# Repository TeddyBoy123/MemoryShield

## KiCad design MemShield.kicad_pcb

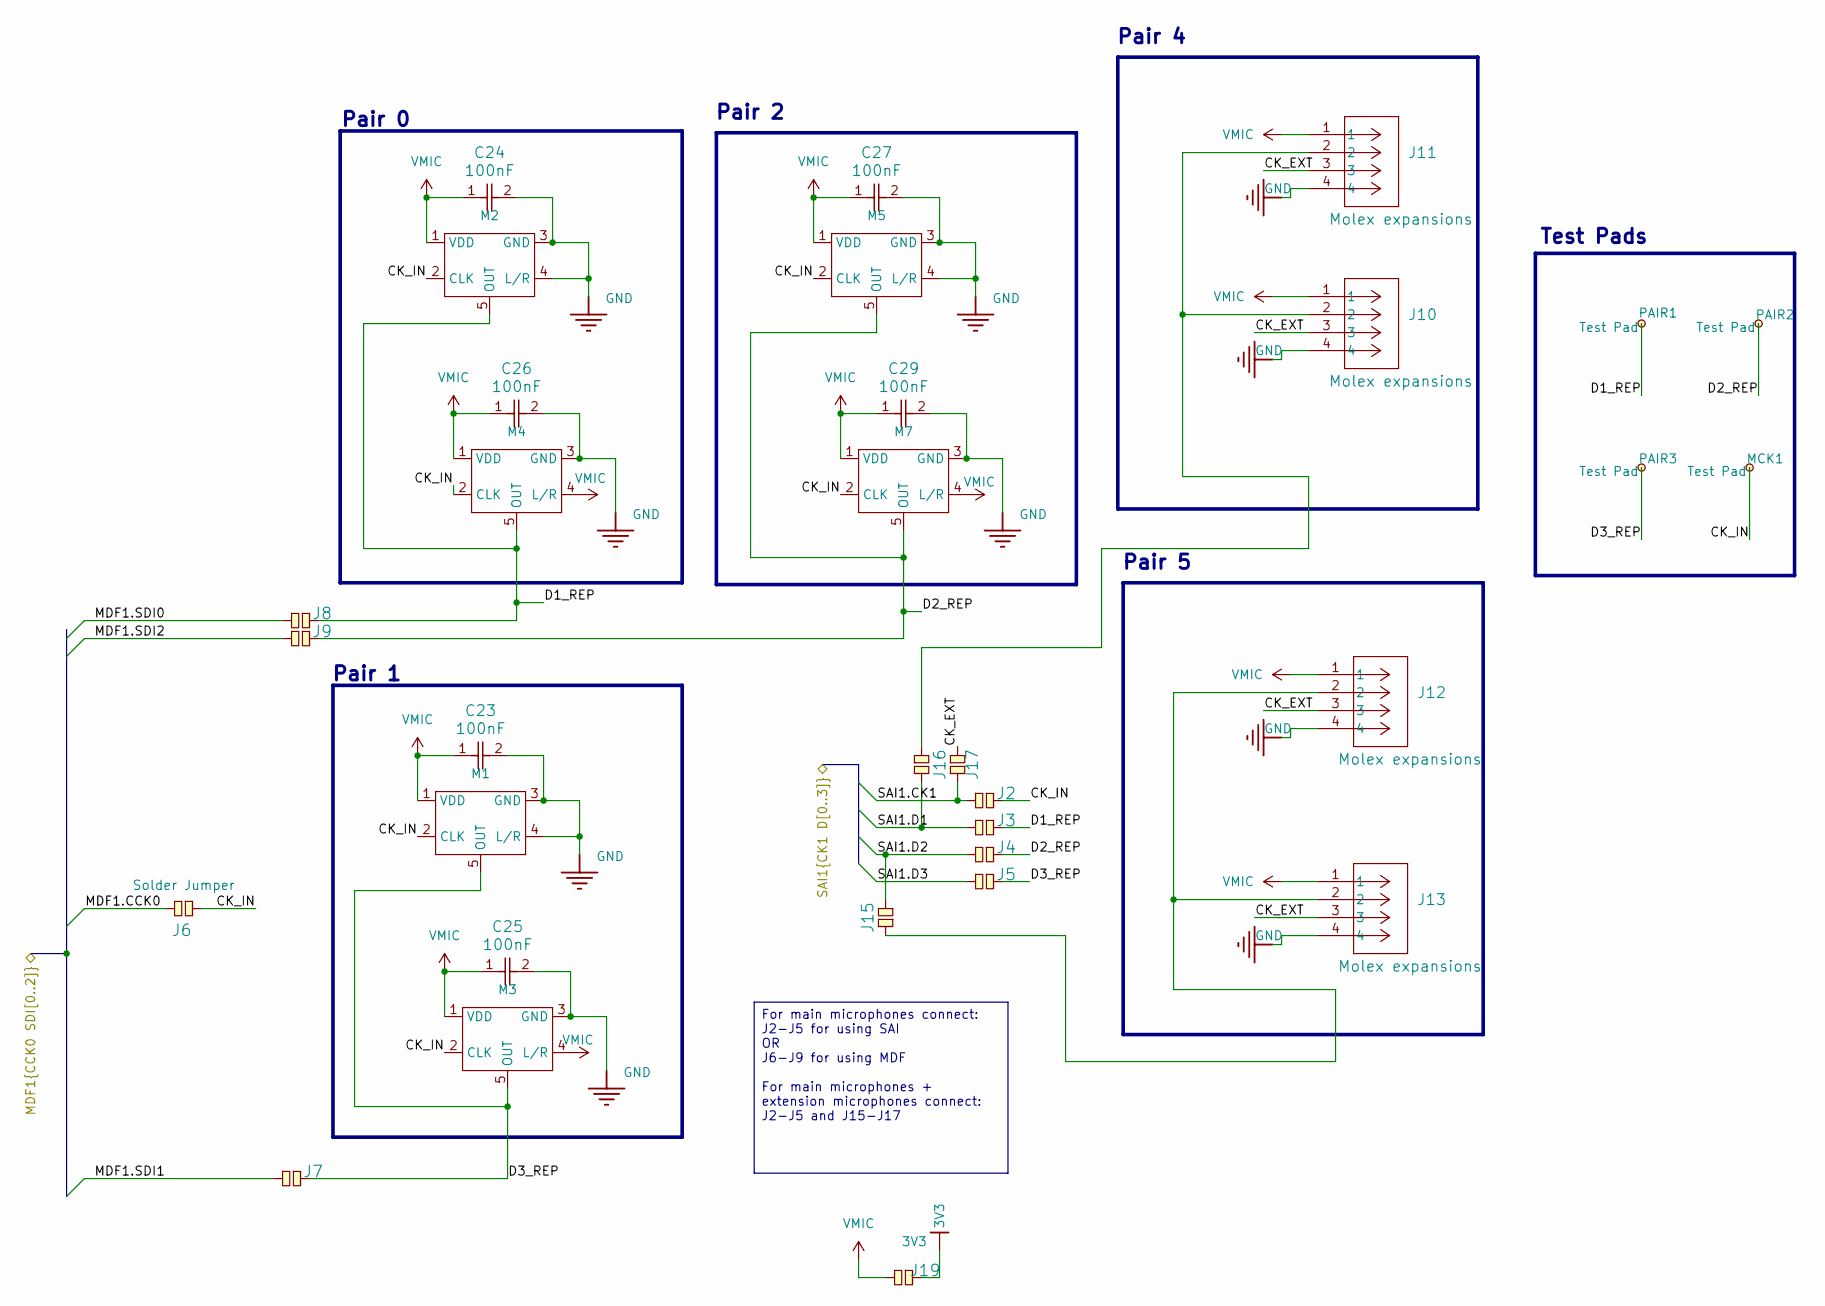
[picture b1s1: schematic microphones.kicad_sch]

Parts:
C23, C24, C25, C26, C27, C29: 100nF; CAP_0402_N_WAL
J2, J3, J4, J5, J6, J7, J8, J9, J15, J16, J17, J19: Solder Jumper; SolderJumper-2_P1.3mm_Open_RoundedPad1.0x1.5mm
J10, J11, J12, J13: Molex expansions; CONN04_530480410_MOL
M1, M2, M3, M4, M5, M7: Microphone; DMM-2627-B
MCK1: Test Pad; TestPoint_Pad_D1.0mm
PAIR1, PAIR2, PAIR3: Test Pad; TestPoint_Pad_D1.0mm

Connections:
3V3: J19.1; also elsewhere on the board
/Core/MDF1.CCK0: J6.2; also elsewhere on the board
/Core/MDF1.SDI0: J8.2; also elsewhere on the board
/Core/MDF1.SDI1: J7.2; also elsewhere on the board
/Core/MDF1.SDI2: J9.2; also elsewhere on the board
/Core/SAI1.CK1: J2.2, J17.2; also elsewhere on the board
/Core/SAI1.D1: J3.2, J16.2; also elsewhere on the board
/Core/SAI1.D2: J4.2, J15.2; also elsewhere on the board
/Core/SAI1.D3: J5.2; also elsewhere on the board
/microphones/CK_EXT: J10.3, J11.3, J12.3, J13.3, J17.1
/microphones/CK_IN: J2.1, J6.1, M1.2 (CLK), M2.2 (CLK), M3.2 (CLK), M4.2 (CLK), M5.2 (CLK), M7.2 (CLK), MCK1.1
/microphones/D1_REP: J3.1, J8.1, M2.5 (OUT), M4.5 (OUT), PAIR1.1
/microphones/D2_REP: J4.1, J9.1, M5.5 (OUT), M7.5 (OUT), PAIR2.1
/microphones/D3_REP: J5.1, J7.1, M1.5 (OUT), M3.5 (OUT), PAIR3.1
GND: C23.2, C24.2, C25.2, C26.2, C27.2, C29.2, J10.4, J11.4, J12.4, J13.4, M1.3 (GND), M1.4 (L/R), M2.3 (GND), M2.4 (L/R), M3.3 (GND), M4.3 (GND), M5.3 (GND), M5.4 (L/R), M7.3 (GND); also elsewhere on the board
unnamed: J10.2, J11.2, J16.1
unnamed: J12.2, J13.2, J15.1
VMIC: C23.1, C24.1, C25.1, C26.1, C27.1, C29.1, J10.1, J11.1, J12.1, J13.1, J19.2, M1.1 (VDD), M2.1 (VDD), M3.1 (VDD), M3.4 (L/R), M4.1 (VDD), M4.4 (L/R), M5.1 (VDD), M7.1 (VDD), M7.4 (L/R)

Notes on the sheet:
Pair 0
Pair 5
Pair 4
Test Pads
Pair 1
Pair 2
For main microphones connect: J2-J5 for using SAI OR J6-J9 for using MDF For main microphones + extension microphones connect: J2-J5 and J15-J17

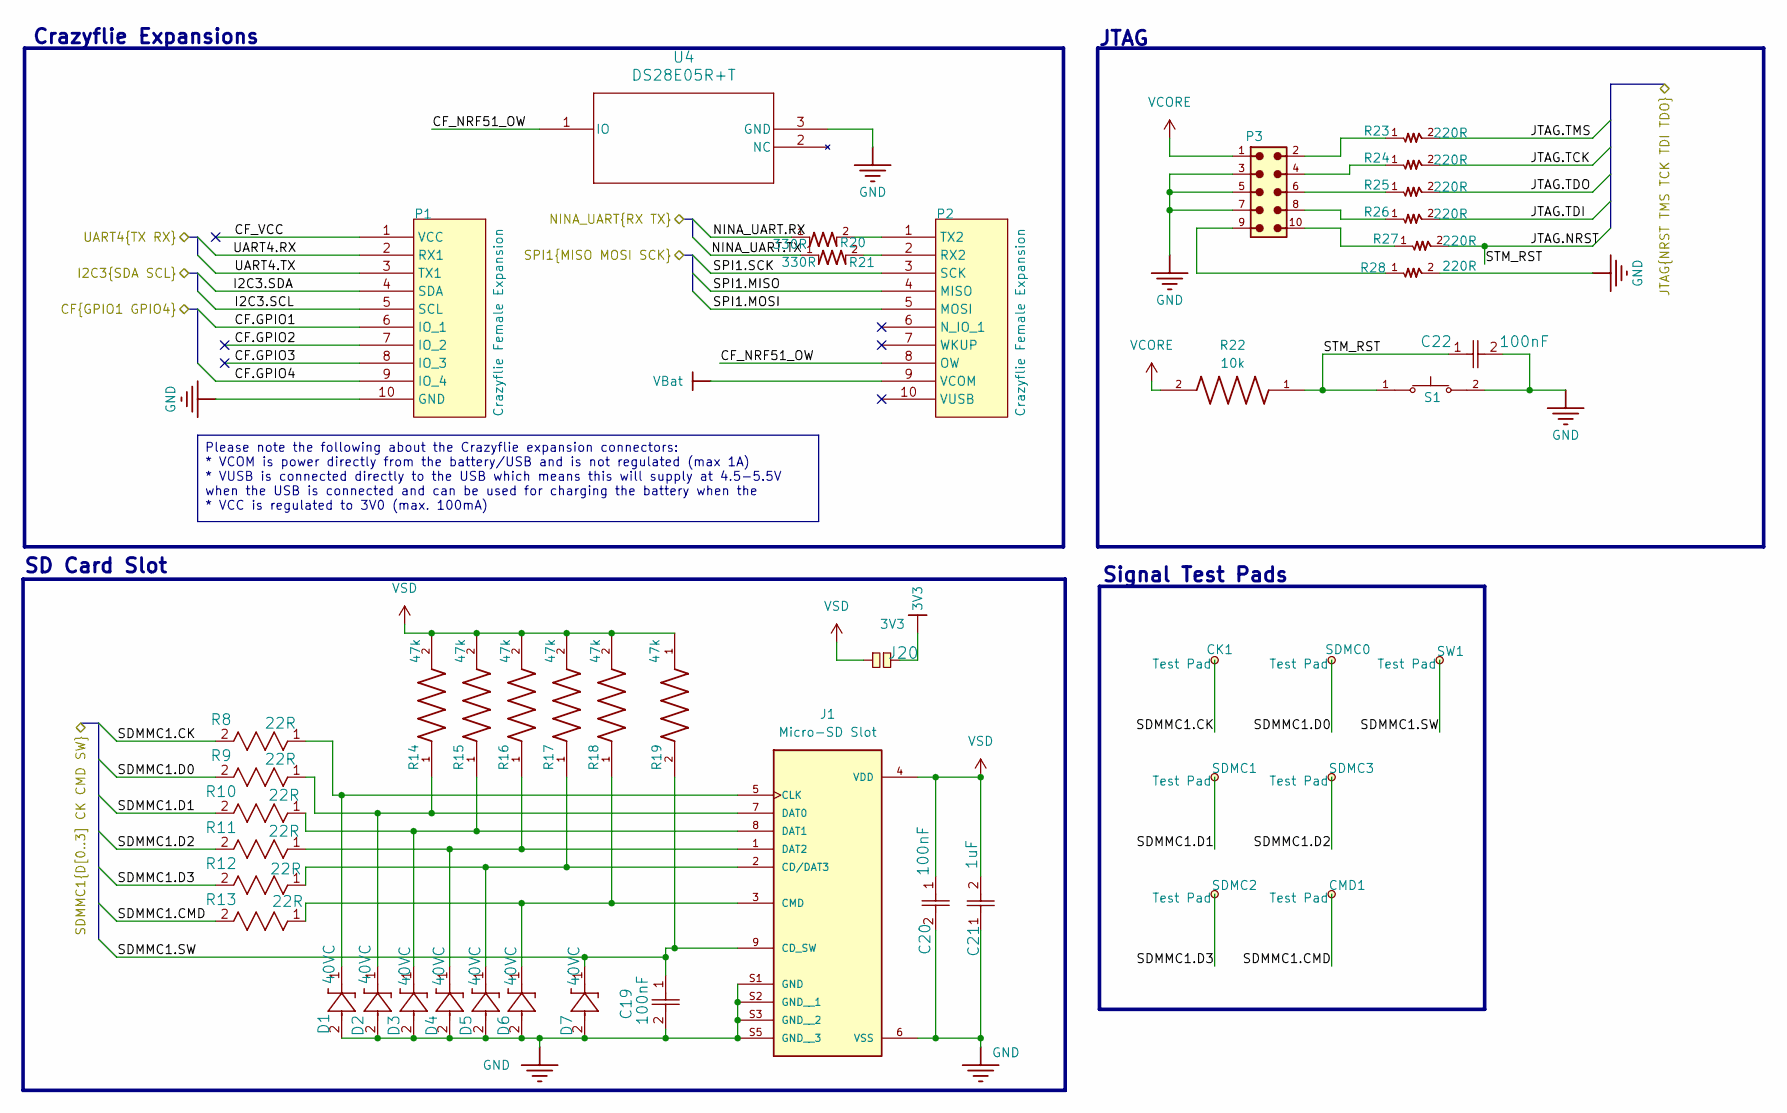
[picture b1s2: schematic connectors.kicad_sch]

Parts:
C19, C20, C22: 100nF; CAP_0402_N_WAL
C21: 1uF; CAP_CL10_SAM
CK1: Test Pad; TestPoint_Pad_D1.0mm
CMD1: Test Pad; TestPoint_Pad_D1.0mm
D1, D2, D3, D4, D5, D6, D7: 40VC; ZDO_PESD0402_LTF
J1: Micro-SD Slot; HRS_DM3CS-SF; PARTREV n/a
J20: Solder Jumper; SolderJumper-2_P1.3mm_Open_RoundedPad1.0x1.5mm
P1, P2: Crazyflie Female Expansion; CF2-DECK-SMD-HOLES
P3: 6220XX21121_62201021121; 62201021121
R8, R9, R10, R11, R12, R13: 22R; RES_CRCW_0402_VIS
R14, R15, R16, R17, R18, R19: 47k; RES_ERJPA3F4702V; PARTREV 3/1/2020; DigiKey_Part_Number P47KBYCT-ND
R20, R21: 330R; RES_ERJH2RD3300X; PARTREV 3/1/2020
R22: 10k; RESC0603X28N
R23, R24, R25, R26, R27, R28: 220R; RESC0603X28N
S1: TS19-32-06-BK-70-1-SMT-TR-67; SW_TS19-32-06-BK-70-1-SMT-TR-67; PARTREV 1.02
SDMC0, SDMC1, SDMC2, SDMC3: Test Pad; TestPoint_Pad_D1.0mm
SW1: Test Pad; TestPoint_Pad_D1.0mm
U4: DS28E05R+T

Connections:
3V3: J20.1; also elsewhere on the board
/Core/CF.GPIO1: P1.6 (IO_1); also elsewhere on the board
/Core/CF.GPIO4: P1.9 (IO_4); also elsewhere on the board
/Core/I2C3.SCL: P1.5 (SCL); also elsewhere on the board
/Core/I2C3.SDA: P1.4 (SDA); also elsewhere on the board
/Core/JTAG.NRST: C22.1, R22.1, R27.2, S1.1; also elsewhere on the board
/Core/JTAG.TCK: R24.2; also elsewhere on the board
/Core/JTAG.TDI: R26.2; also elsewhere on the board
/Core/JTAG.TDO: R25.2; also elsewhere on the board
/Core/JTAG.TMS: R23.2; also elsewhere on the board
/Core/SDMMC1.CK: CK1.1, R8.2; also elsewhere on the board
/Core/SDMMC1.CMD: CMD1.1, R13.2; also elsewhere on the board
/Core/SDMMC1.D0: R9.2, SDMC0.1; also elsewhere on the board
/Core/SDMMC1.D1: R10.2, SDMC1.1; also elsewhere on the board
/Core/SDMMC1.D2: R11.2, SDMC3.1; also elsewhere on the board
/Core/SDMMC1.D3: R12.2, SDMC2.1; also elsewhere on the board
/Core/SDMMC1.SW: C19.1, D7.1, J1.9 (CD_SW), R19.2, SW1.1; also elsewhere on the board
/Core/SPI1.MISO: P2.4 (MISO); also elsewhere on the board
/Core/SPI1.MOSI: P2.5 (MOSI); also elsewhere on the board
/Core/SPI1.SCK: P2.3 (SCK); also elsewhere on the board
/Core/UART4.RX: P1.2 (RX1); also elsewhere on the board
/Core/UART4.TX: P1.3 (TX1); also elsewhere on the board
/connectors/CF.GPIO2: P1.7 (IO_2)
/connectors/CF.GPIO2_1: P1.7 (IO_2)
/connectors/CF.GPIO2_2: P1.7 (IO_2)
/connectors/CF.GPIO3: P1.8 (IO_3)
/connectors/CF.GPIO3_1: P1.8 (IO_3)
/connectors/CF.GPIO3_2: P1.8 (IO_3)
/connectors/CF_NRF51_OW: P2.8 (OW), U4.1 (IO)
/connectors/CF_VCC: P1.1 (VCC)
/connectors/CF_VCC_1: P1.1 (VCC)
/connectors/CF_VCC_2: P1.1 (VCC)
/connectors/NINA_UART.RX: R20.1; also elsewhere on the board
/connectors/NINA_UART.TX: R21.1; also elsewhere on the board
GND: C19.2, C20.2, C21.1, C22.2, D1.2, D2.2, D3.2, D4.2, D5.2, D6.2, D7.2, J1.6 (VSS), J1.S1 (GND), J1.S2 (GND__1), J1.S3 (GND__2), J1.S5 (GND__3), P1.10 (GND), P3.3, P3.5, P3.7, R28.2, S1.2, U4.3 (GND); also elsewhere on the board
unnamed: D5.1, J1.2 (CD/DAT3), R12.1, R17.1
unnamed: D1.1, J1.5 (CLK), R8.1
unnamed: D6.1, J1.3 (CMD), R13.1, R18.1
unnamed: D2.1, J1.7 (DAT0), R9.1, R14.1
unnamed: D3.1, J1.8 (DAT1), R10.1, R15.1
unnamed: D4.1, J1.1 (DAT2), R11.1, R16.1
unnamed: P2.2 (RX2), R21.2
unnamed: P2.1 (TX2), R20.2
unnamed: P3.2, R23.1
unnamed: P3.4, R24.1
unnamed: P3.6, R25.1
unnamed: P3.8, R26.1
unnamed: P3.9, R28.1
unnamed: P3.10, R27.1
VBat: P2.9 (VCOM); also elsewhere on the board
VCORE: P3.1, R22.2; also elsewhere on the board
VSD: C20.1, C21.2, J1.4 (VDD), J20.2, R14.2, R15.2, R16.2, R17.2, R18.2, R19.1

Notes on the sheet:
Crazyflie Expansions
Signal Test Pads
JTAG
SD Card Slot
Please note the following about the Crazyflie expansion connectors: * VCOM is power directly from the battery/USB and is not regulated (max 1A) * VUSB is connected directly to the USB which means this will supply at 4.5-5.5V when the USB is connected and can be used for charging the battery when th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

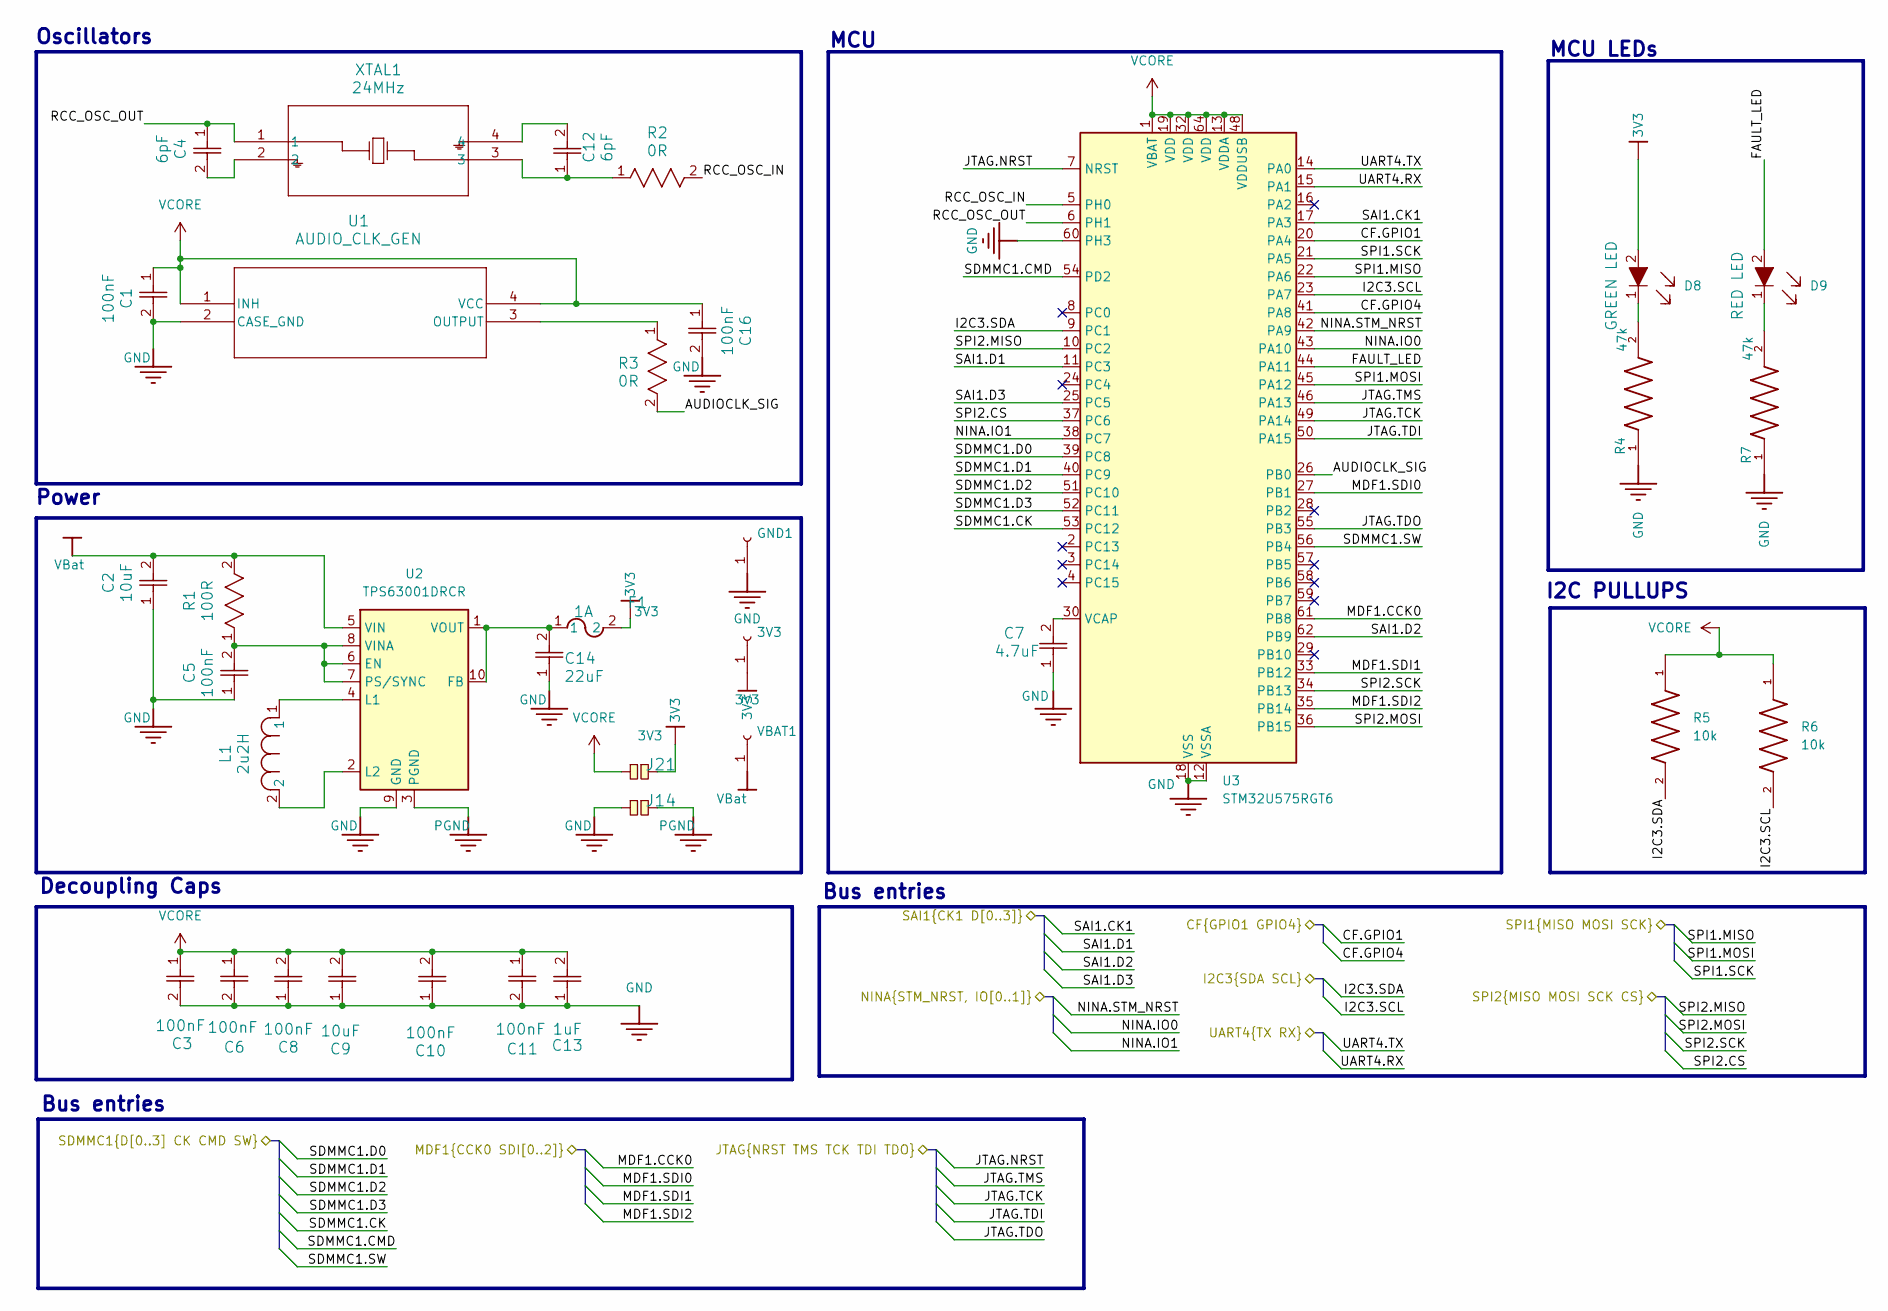
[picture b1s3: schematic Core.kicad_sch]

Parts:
3V3: 3V3; PinHeader_1x01_P2.54mm_Vertical
C1, C3, C5, C6, C8, C10, C11, C16: 100nF; CAP_0402_N_WAL
C2, C9: 10uF; CAP_CL10_SAM
C4, C12: 6pF; CAPC6333_33N_KEM
C7: 4.7uF; CAP_CL05_SAM
C13: 1uF; CAP_CL10_SAM
C14: 22uF; CAP_CL_05_SAM
D8: GREEN LED; LED_0603; MPN LTST-C190GKT; Digi-Key_PN 160-1183-1-ND
D9: RED LED; LED_0603; MPN LTST-C191KRKT; Digi-Key_PN 160-1447-1-ND
F1: 1A; 0ZCK_BEL
GND1: GND1; PinHeader_1x01_P2.54mm_Vertical
J14, J21: Solder Jumper; SolderJumper-2_P1.3mm_Open_RoundedPad1.0x1.5mm
L1: 2u2H; IND_VLS3012HBX_TDK
R1: 100R; RC0603N_VIS
R2, R3: 0R; STA_RMCF0603_STP
R4, R7: 47k; RES_ERJPA3F4702V; PARTREV 3/1/2020; DigiKey_Part_Number P47KBYCT-ND
R5, R6: 10k; RESC0603X28N
U1: AUDIO_CLK_GEN; OSC_KC2016Z_KYO
U2: TPS63001DRCR; Texas_DRC0010J_ThermalVias
U3: STM32U575RGT6; LQFP-64_10x10mm_P0.5mm
VBAT1: GND1; PinHeader_1x01_P2.54mm_Vertical
XTAL1: 24MHz; NX3225SA-24.000M-STD-CSR-1_NDK

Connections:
3V3: 3V3.1, D8.2, F1.2, J21.1; also elsewhere on the board
/Core/AUDIOCLK_SIG: R3.2, U3.26 (PB0)
/Core/CF.GPIO1: U3.20 (PA4); also elsewhere on the board
/Core/CF.GPIO4: U3.41 (PA8); also elsewhere on the board
/Core/FAULT_LED: D9.2, U3.44 (PA11)
/Core/I2C3.SCL: R6.2, U3.23 (PA7); also elsewhere on the board
/Core/I2C3.SDA: R5.2, U3.9 (PC1); also elsewhere on the board
/Core/JTAG.NRST: U3.7 (NRST); also elsewhere on the board
/Core/JTAG.TCK: U3.49 (PA14); also elsewhere on the board
/Core/JTAG.TDI: U3.50 (PA15); also elsewhere on the board
/Core/JTAG.TDO: U3.55 (PB3); also elsewhere on the board
/Core/JTAG.TMS: U3.46 (PA13); also elsewhere on the board
/Core/MDF1.CCK0: U3.61 (PB8); also elsewhere on the board
/Core/MDF1.SDI0: U3.27 (PB1); also elsewhere on the board
/Core/MDF1.SDI1: U3.33 (PB12); also elsewhere on the board
/Core/MDF1.SDI2: U3.35 (PB14); also elsewhere on the board
/Core/NINA.IO0: U3.43 (PA10); also elsewhere on the board
/Core/NINA.IO1: U3.38 (PC7); also elsewhere on the board
/Core/NINA.STM_NRST: U3.42 (PA9); also elsewhere on the board
/Core/RCC_OSC_IN: R2.2, U3.5 (PH0)
/Core/RCC_OSC_OUT: C4.1, U3.6 (PH1), XTAL1.1; also elsewhere on the board
/Core/SAI1.CK1: U3.17 (PA3); also elsewhere on the board
/Core/SAI1.D1: U3.11 (PC3); also elsewhere on the board
/Core/SAI1.D2: U3.62 (PB9); also elsewhere on the board
/Core/SAI1.D3: U3.25 (PC5); also elsewhere on the board
/Core/SDMMC1.CK: U3.53 (PC12); also elsewhere on the board
/Core/SDMMC1.CMD: U3.54 (PD2); also elsewhere on the board
/Core/SDMMC1.D0: U3.39 (PC8); also elsewhere on the board
/Core/SDMMC1.D1: U3.40 (PC9); also elsewhere on the board
/Core/SDMMC1.D2: U3.51 (PC10); also elsewhere on the board
/Core/SDMMC1.D3: U3.52 (PC11); also elsewhere on the board
/Core/SDMMC1.SW: U3.56 (PB4); also elsewhere on the board
/Core/SPI1.MISO: U3.22 (PA6); also elsewhere on the board
/Core/SPI1.MOSI: U3.45 (PA12); also elsewhere on the board
/Core/SPI1.SCK: U3.21 (PA5); also elsewhere on the board
/Core/SPI2.CS: U3.37 (PC6); also elsewhere on the board
/Core/SPI2.MISO: U3.10 (PC2); also elsewhere on the board
/Core/SPI2.MOSI: U3.36 (PB15); also elsewhere on the board
/Core/SPI2.SCK: U3.34 (PB13); also elsewhere on the board
/Core/UART4.RX: U3.15 (PA1); also elsewhere on the board
/Core/UART4.TX: U3.14 (PA0); also elsewhere on the board
GND: C1.2, C2.1, C3.2, C5.1, C6.2, C7.1, C8.1, C9.1, C10.1, C11.2, C13.1, C14.1, C16.2, GND1.1, J14.2, R4.1, R7.1, U1.2 (CASE_GND), U2.9 (GND), U3.12 (VSSA), U3.18 (VSS), U3.31 (VSS), U3.47 (VSS), U3.60 (PH3), U3.63 (VSS); also elsewhere on the board
unnamed 67: C4.2, XTAL1.2; also elsewhere on the board
unnamed 68: C12.1, R2.1, XTAL1.3; also elsewhere on the board
unnamed 69: C12.2, XTAL1.4; also elsewhere on the board
unnamed: D8.1, R4.2
unnamed: D9.1, R7.2
unnamed: R3.1, U1.3 (OUTPUT)
unnamed: C5.2, R1.1, U2.6 (EN), U2.7 (PS/SYNC), U2.8 (VINA)
unnamed: C14.2, F1.1, U2.1 (VOUT), U2.10 (FB)
unnamed: L1.1, U2.4 (L1)
unnamed: L1.2, U2.2 (L2)
unnamed: C7.2, U3.30 (VCAP)
PGND: J14.1, U2.3 (PGND), U2.11 (PGND)
VBat: C2.2, R1.2, U2.5 (VIN), VBAT1.1; also elsewhere on the board
VCORE: C1.1, C3.1, C6.1, C8.2, C9.2, C10.2, C11.1, C13.2, C16.1, J21.2, R5.1, R6.1, U1.1 (INH), U1.4 (VCC), U3.1 (VBAT), U3.13 (VDDA), U3.19 (VDD), U3.32 (VDD), U3.48 (VDDUSB), U3.64 (VDD); also elsewhere on the board

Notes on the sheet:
Decoupling Caps
Bus entries
Power
MCU LEDs
I2C PULLUPS
MCU
Oscillators

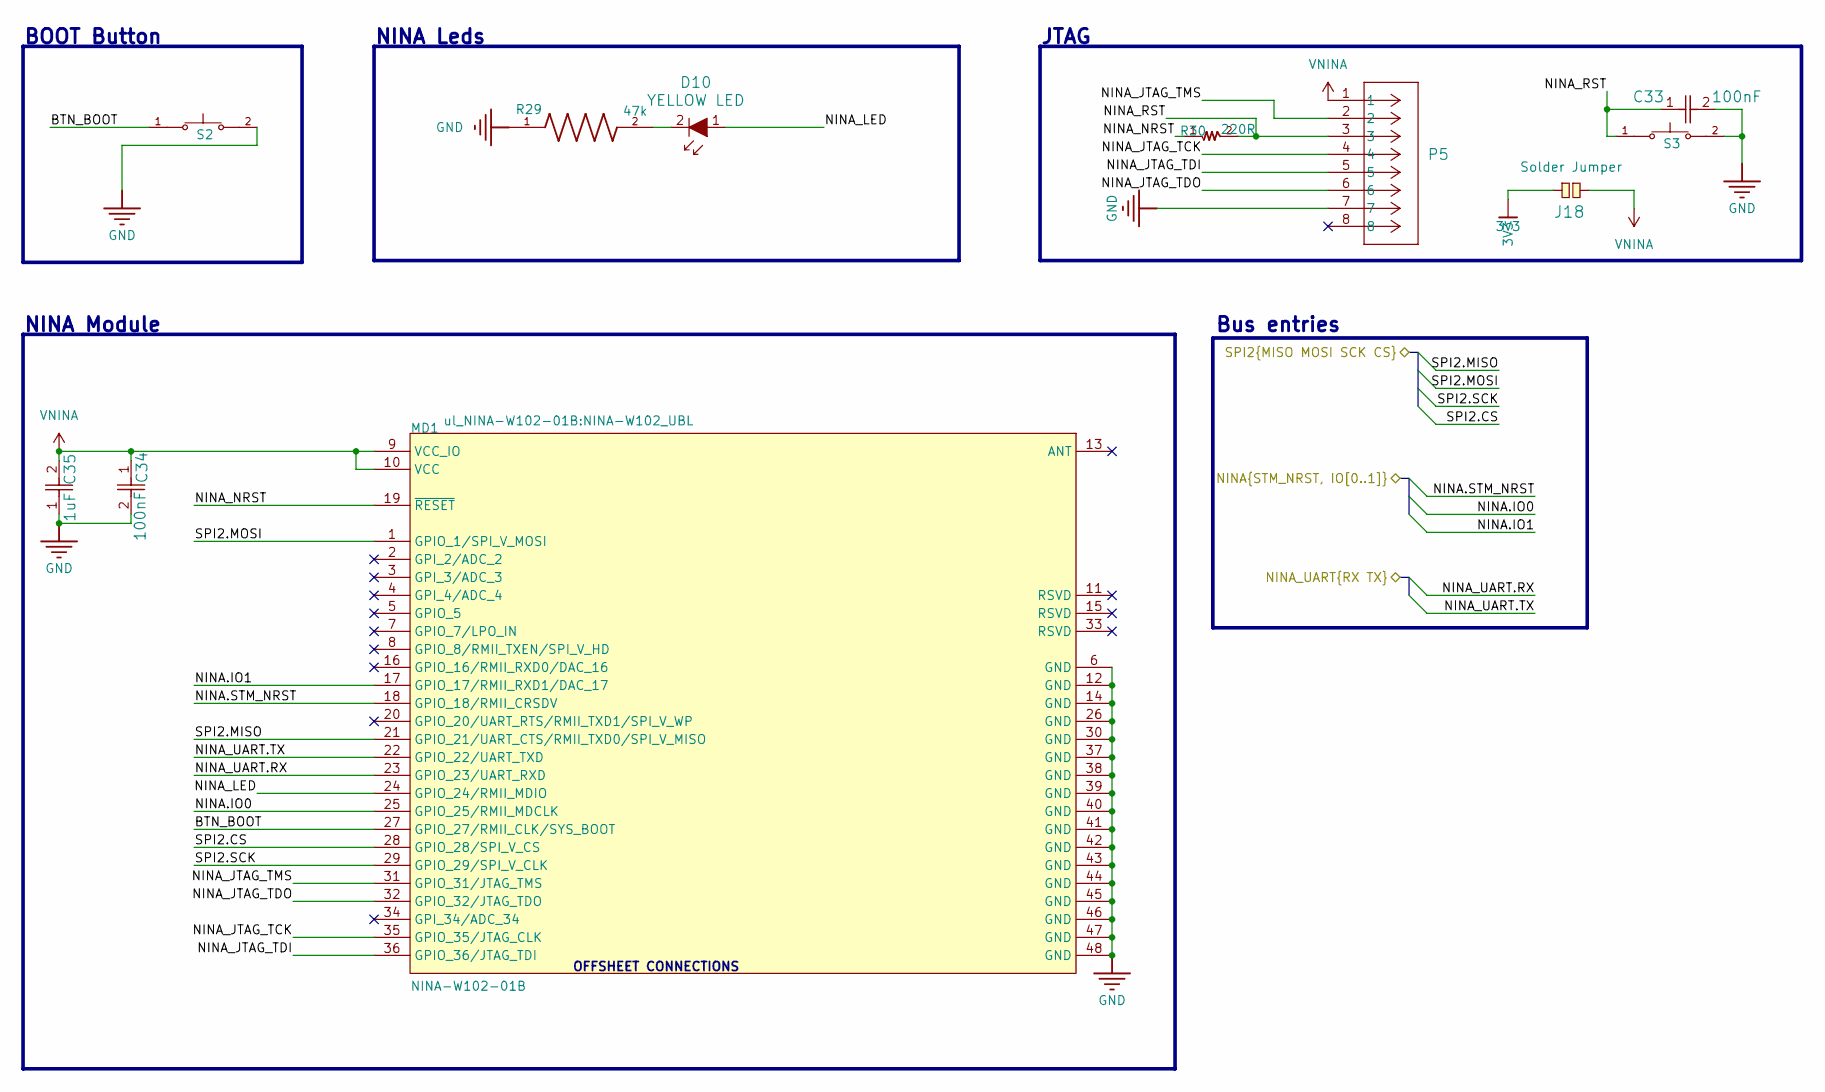
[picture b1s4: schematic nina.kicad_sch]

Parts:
C33, C34: 100nF; CAP_0402_N_WAL
C35: 1uF; CAP_CL10_SAM
D10: YELLOW LED; 0603; MPN LTST-C190KSKT; Digi-Key_PN 160-1437-1-ND
J18: Solder Jumper; SolderJumper-2_P1.3mm_Open_RoundedPad1.0x1.5mm
MD1: NINA-W102-01B; NINA-W102_UBL; MANUFACTURER PART NUMBER NINA-W102-00B-00; DIGIKEY DESCRIPTION STAND-ALONE MULTIRADIO MODULES
P5: GRPB042VWVN-RC; CONN8_VWVN-RC_SUL
R29: 47k; RES_ERJPA3F4702V; PARTREV 3/1/2020; DigiKey_Part_Number P47KBYCT-ND
R30: 220R; RESC0603X28N
S2, S3: TS19-32-06-BK-70-1-SMT-TR-67; SW_TS19-32-06-BK-70-1-SMT-TR-67; PARTREV 1.02

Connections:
3V3: J18.2; also elsewhere on the board
/Core/NINA.IO0: MD1.25 (GPIO_25/RMII_MDCLK); also elsewhere on the board
/Core/NINA.IO1: MD1.17 (GPIO_17/RMII_RXD1/DAC_17); also elsewhere on the board
/Core/NINA.STM_NRST: MD1.18 (GPIO_18/RMII_CRSDV); also elsewhere on the board
/Core/SPI2.CS: MD1.28 (GPIO_28/SPI_V_CS); also elsewhere on the board
/Core/SPI2.MISO: MD1.21 (GPIO_21/UART_CTS/RMII_TXD0/SPI_V_MISO); also elsewhere on the board
/Core/SPI2.MOSI: MD1.1 (GPIO_1/SPI_V_MOSI); also elsewhere on the board
/Core/SPI2.SCK: MD1.29 (GPIO_29/SPI_V_CLK); also elsewhere on the board
/connectors/NINA_UART.RX: MD1.23 (GPIO_23/UART_RXD); also elsewhere on the board
/connectors/NINA_UART.TX: MD1.22 (GPIO_22/UART_TXD); also elsewhere on the board
/nina/BTN_BOOT: MD1.27 (GPIO_27/RMII_CLK/SYS_BOOT), S2.1
/nina/NINA_JTAG_TCK: MD1.35 (GPIO_35/JTAG_CLK), P5.4
/nina/NINA_JTAG_TDI: MD1.36 (GPIO_36/JTAG_TDI), P5.5
/nina/NINA_JTAG_TDO: MD1.32 (GPIO_32/JTAG_TDO), P5.6
/nina/NINA_JTAG_TMS: MD1.31 (GPIO_31/JTAG_TMS), P5.2
/nina/NINA_LED: D10.1, MD1.24 (GPIO_24/RMII_MDIO)
/nina/NINA_NRST: MD1.19 (~RESET), R30.1
/nina/NINA_RST: C33.1, P5.3, R30.2, S3.1
GND: C33.2, C34.2, C35.1, MD1.6 (GND), MD1.12 (GND), MD1.14 (GND), MD1.26 (GND), MD1.30 (GND), MD1.37 (GND), MD1.38 (GND), MD1.39 (GND), MD1.40 (GND), MD1.41 (GND), MD1.42 (GND), MD1.43 (GND), MD1.44 (GND), MD1.45 (GND), MD1.46 (GND), MD1.47 (GND), MD1.48 (GND), P5.7, R29.1, S2.2, S3.2; also elsewhere on the board
unnamed: D10.2, R29.2
VNINA: C34.1, C35.2, J18.1, MD1.9 (VCC_IO), MD1.10 (VCC), P5.1

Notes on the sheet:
JTAG
Bus entries
NINA Leds
NINA Module
BOOT Button
OFFSHEET CONNECTIONS

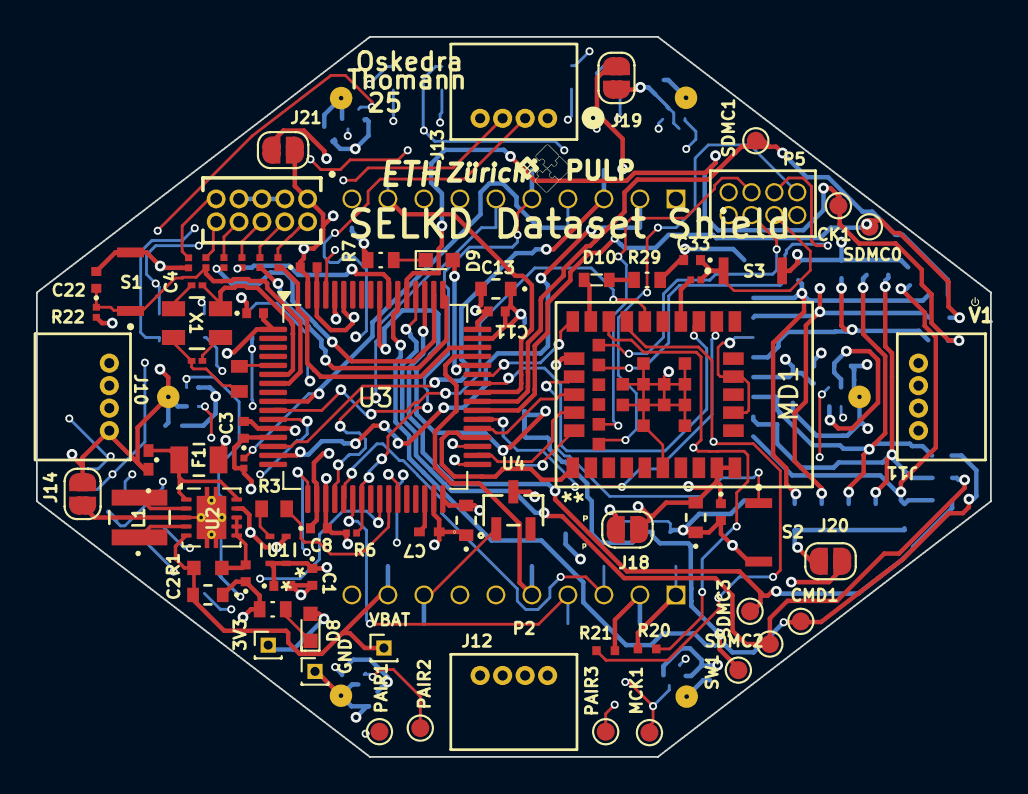
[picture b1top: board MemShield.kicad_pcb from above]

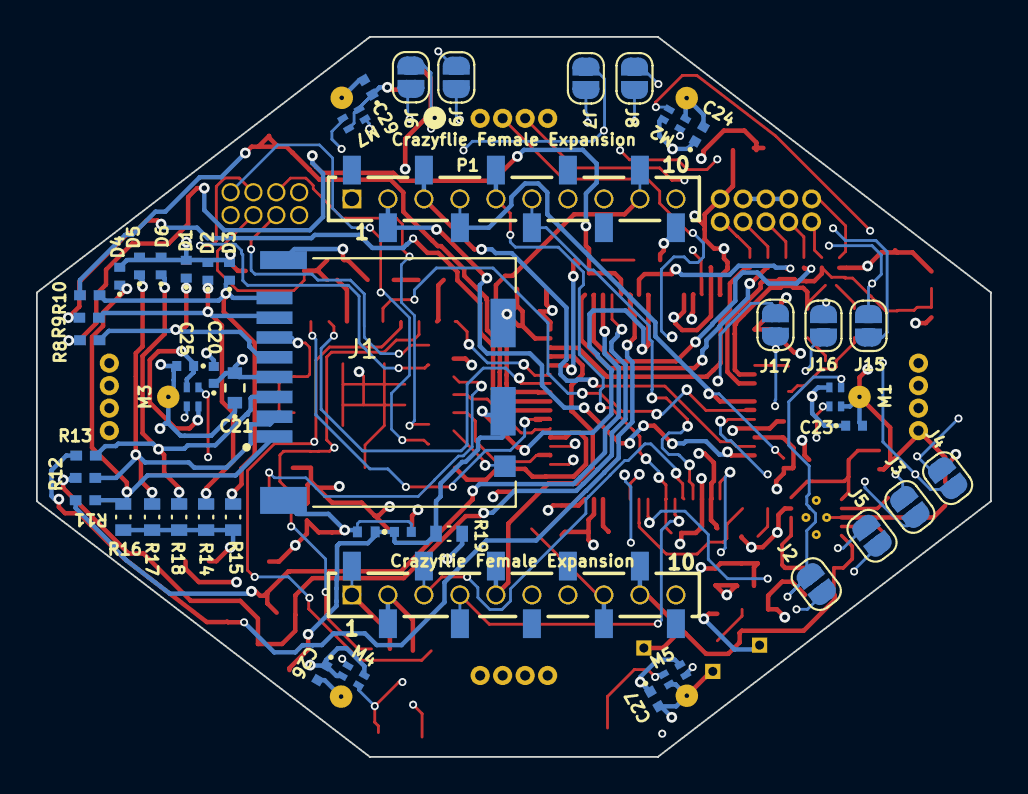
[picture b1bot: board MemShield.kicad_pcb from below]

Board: 6 copper layers, 53.0 x 40.0 mm, 124 parts (48 on the bottom side), 92 nets.

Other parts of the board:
GND: GND1; PinHeader_1x01_P1.00mm_Vertical
VBAT: GND1; PinHeader_1x01_P1.00mm_Vertical
X1: 24MHz; NX3225SA-24.000M-STD-CSR-1_NDK

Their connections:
/Core/RCC_OSC_OUT: X1.1; also elsewhere on the board
GND: GND.1; also elsewhere on the board
unnamed 67: X1.2; also elsewhere on the board
unnamed 68: X1.3; also elsewhere on the board
unnamed 69: X1.4; also elsewhere on the board
VBat: VBAT.1; also elsewhere on the board

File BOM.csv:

"Reference","Qty","Value","DNP","Exclude from BOM","Exclude from Board","Datasheet"
"3V3,BVBAT1,CK1,CMD1,GND1,MCK1,PAIR1,PAIR2,PAIR3,SDMC0,SDMC1,SDMC2,SDMC3,SW1","14","Test Pad","","","",""
"C1,C3,C5,C6,C8,C10,C11,C16,C19,C20,C22,C23,C24,C25,C26,C27,C29,C33,C34","19","100nF","","","","https://www.digikey.ch/de/products/detail/walsin-technology-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"
"C2,C9","2","10uF","","","","https://www.digikey.ch/de/products/detail/samsung-electro-me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"
"C4,C12","2","6pF","","","","https://www.digikey.ch/en/products/detail/kemet/CBR02C609C8G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"
"C7","1","4.7uF","","","","https://www.digikey.ch/en/products/detail/samsung-electro-me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"
"C13,C21,C35","3","1uF","","","","https://www.digikey.ch/en/products/detail/samsung-electro-me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"
"C14","1","22uF","","","","https://www.digikey.ch/de/products/detail/samsung-electro-me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"
"D1,D2,D3,D4,D5,D6,D7","7","40VC","","","","https://www.digikey.ch/de/products/detail/littelfuse-inc/pes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"
"D8","1","GREEN LED","","","","https://www.digikey.ch/de/products/detail/liteon/LTST-C190GK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"
"D9","1","RED LED","","","","https://www.digikey.ch/de/products/detail/liteon/LTST-C191KR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"
"D10","1","YELLOW LED","","","","https://www.digikey.ch/de/products/detail/lite-on-inc/ltst-c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"
"F1","1","1A","","","","https://www.digikey.ch/de/products/detail/bel-fuse-inc/0ZCK0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"
"J1","1","Micro-SD Slot","","","","https://www.digikey.ch/de/products/detail/hirose-electric-co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"
"J2,J3,J4,J5,J6,J7,J8,J9,J14,J15,J16,J17","12","Solder Jumper","","","",""
"J10,J11,J12,J13","4","Molex expansions","","","","https://www.digikey.ch/de/products/detail/molex/0530480410/2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"
"L1","1","2u2H","","","","https://www.digikey.ch/de/products/detail/tdk-corporation/VL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"
"M1,M2,M3,M4,M5,M7","6","Microphone","","","","https://www.digikey.ch/de/products/detail/pui-audio-inc/DMM-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"
"MD1","1","NINA-W102-01B","","","","https://www.digikey.ch/de/products/detail/u-blox/NINA-W102-0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"
"P1,P2","2","Crazyflie Female Expansion","","","","https://store.bitcraze.io/collections/decks/products/female-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"
"P3","1","6220XX21121_62201021121","","","","https://www.digikey.ch/de/products/detail/w%C3%BCrth-elektro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"
"P5","1","GRPB042VWVN-RC","","","","https://www.digikey.ch/de/products/detail/sullins-connector-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"
"R1","1","100R","","","","https://www.digikey.ch/de/products/detail/yageo/RC0603FR-071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"
"R2,R3","2","0R","","","","https://www.digikey.ch/de/products/detail/stackpole-electron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"
"R4,R7,R14,R15,R16,R17,R18,R19,R29","9","47k","","","","https://www.digikey.ch/de/products/detail/panasonic-electron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"
"R5,R6,R22","3","10k","","","","https://www.digikey.ch/de/products/detail/vishay-dale/CRCW02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"
"R8,R9,R10,R11,R12,R13","6","22R","","","","https://www.digikey.ch/de/products/detail/vishay-dale/CRCW04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"
"R20,R21","2","330R","","","","https://www.digikey.ch/de/products/detail/panasonic-electron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"
"R23,R24,R25,R26,R27,R28,R30","7","220R","","","","https://www.digikey.ch/de/products/detail/vishay-dale/CRCW02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"
"S1,S2,S3","3","TS19-32-06-BK-70-1-SMT-TR-67","","","","https://www.digikey.ch/de/products/detail/same-sky-formerly-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"
"U1","1","AUDIO_CLK_GEN","","","","https://www.digikey.ch/de/products/detail/kyocera-avx/KC2016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"
"U2","1","TPS63001DRCR","","","","https://www.digikey.ch/de/products/detail/texas-instruments/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"
"U3","1","STM32U575RGT6","","","","https://www.digikey.ch/de/products/detail/stmicroelectronics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"
"U4","1","DS28E05R+T","","","","https://www.digikey.ch/de/products/detail/analog-devices-inc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"
"XTAL1","1","24MHz","","","","https://www.digikey.ch/de/products/detail/ndk-nihon-dempa-ko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"

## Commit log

2025-12-11 power planes
2025-12-21 seb commit
2025-12-28 fixes v1
    sd cmd line
    sd resistors
    designator placement
    mirrored microphones
2026-01-01 fabrication seb
2026-01-10 fab2
2026-01-10 fab3
2026-01-10 fab4
